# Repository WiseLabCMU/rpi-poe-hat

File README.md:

# RPi Power-over-Ethernet Hat

Give your RPi-0 ethernet and Power-ver-Ethernet (POE).  The hat uses the ENC28J60 chipset from Microchip to provide an 10Base-T 802.3af compatible interface for your RPi over SPI. The board negotiates power from your POE-enabled switch shared between 5V and 3.3V outputs at up to 9 Watts.

## Hardware Overview

### Jumpers

Placing a 0603 jumper across J1 pulls the EEPROM WP line high, preventing writes.

J2 can be used to choose a chip select on the SPI bus. By default, CS0 is connected by a trace under one of the jumpers. To change it, cut the trace with a hobby knife and place a 0603 jumper across the right-most pads in the previous picture

## Configuring your RPi

For the latest Raspbian image, go to https://www.raspberrypi.org/downloads/raspbian/. 

### Enable SPI

1. run `raspi-config` 
2. select `9 Advanced Options`
3. select `A6 SPI`
4. select `yes` to enbale SPI
5. select `yes` to automaticaly load kernel module
6. select `<Finish>`
7. select `yes` to reboot

### Enable ENC28J60 Overlay

Add the this line to the `/boot/congig.txt`:

`dtoverlay=enc28j60`

After this line is added the Raspberry Pi will automatically load the device on boot.

## Files and Directories

`hardware/RPI0E.sch` - Eagle CAD schematic for the hat.

`hardware/RPI0E.brd` - Eagle CAD board for the hat.

`hardware/bom.xlsx` - Spreadsheet with bill of materials

`hardware/datasheets/` - datasheets for the board components, as well as some part drawings.

For information on EEPROM configuration visit https://github.com/raspberrypi/hats .

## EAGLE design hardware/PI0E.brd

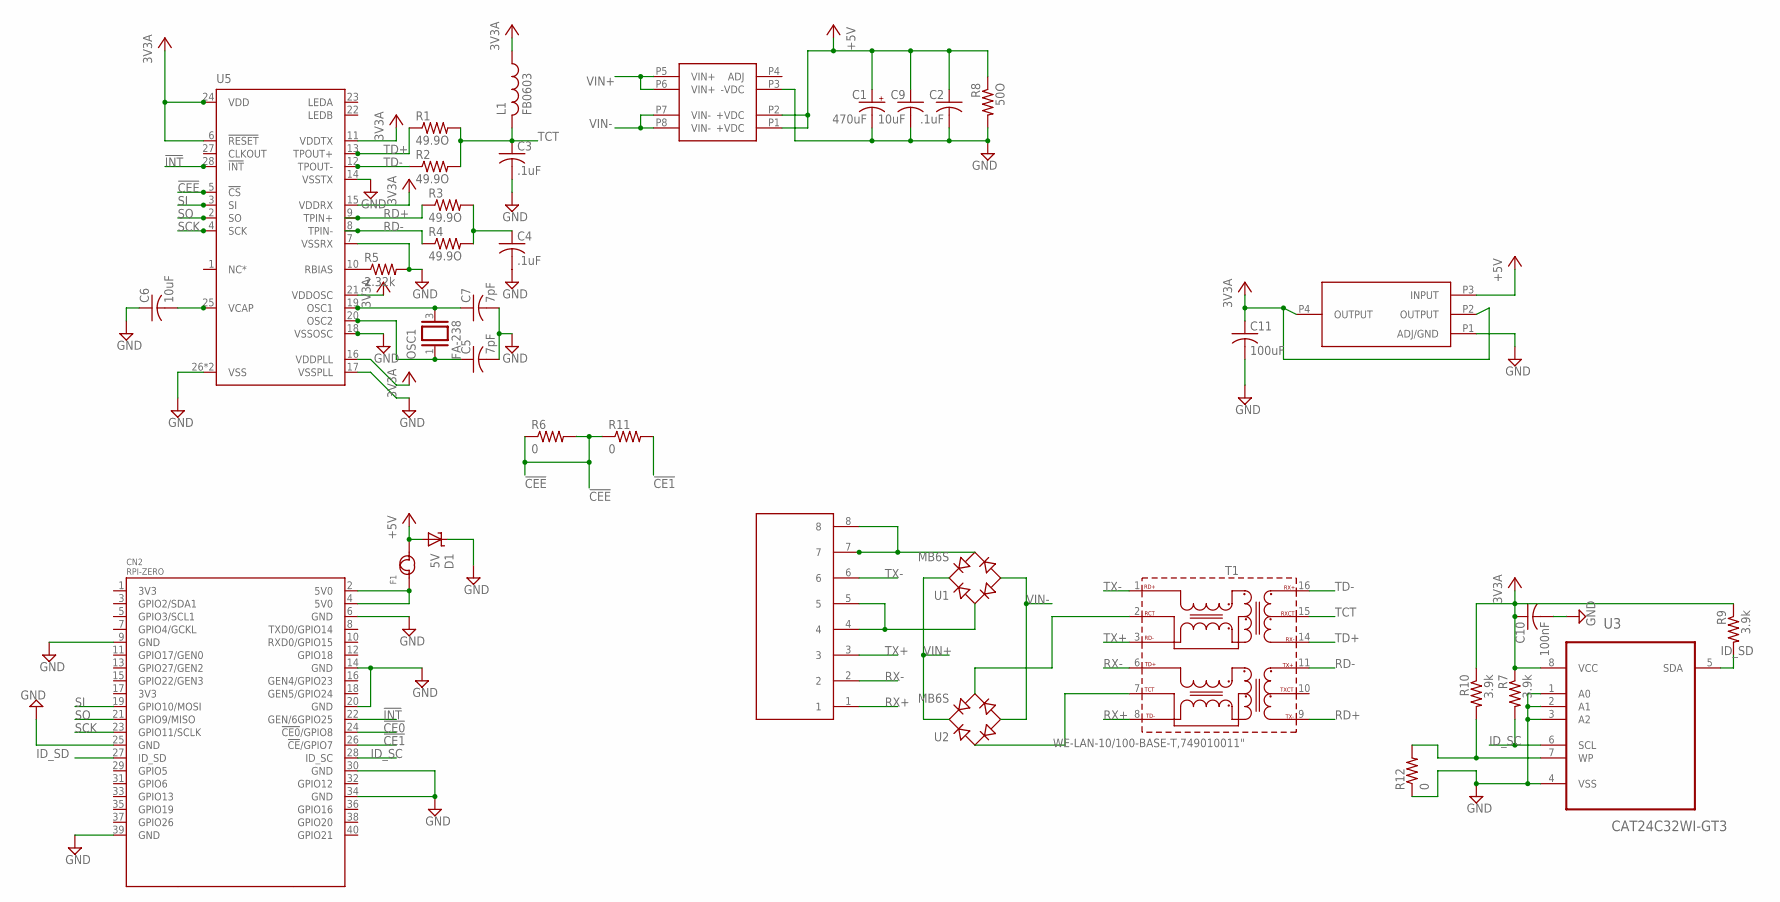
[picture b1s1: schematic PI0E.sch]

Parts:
C1: 470uF; PANASONIC_F
C2, C3, C4: .1uF; C0603
C5, C7: 7pF; C0603
C6, C9: 10uF; C0603
C10: 100nF; C0603
C11: 100uF; C0805
CN1: RJCSEX38X01XRJCSEX38X01X; RJCSEX38X01X
CN2: RPI-ZERO; RASPBERRYPI_BASTELSTUBE_V13_RASPI_BOARD_B+_FULL
D1: 5V; SMBJ
F1: FUSE'1812'; F1812
L1: FB0603; R0603
OSC1: FA-238
R1, R2, R3, R4: 49.9O; R0603
R5: 2.32k; R0603
R6, R11, R12: 0; R0603
R7, R9, R10: 3.9k; R0603
R8: 50O; R0603
T1: WE-LAN-10/100-BASE-T,749010011"; 749010011
U1, U2: MB6S; SOIC-4
U3: CAT24C32WI-GT3; SOIC127P600X175-8N
U4: TLV1117TLV1117DCY; SOT-223
U5: ENC28J60QFN28-ML_6X6MM; QFN28-ML_6X6MM
U6: AG9800AG9800M; AG9800M

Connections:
5V0@1: CN2.2 (5V0), CN2.4 (5V0), F1.1
!CE0: CN2.24 (!CE0!/GPIO8)
!CE1: CN2.26 (!CE!/GPIO7), R11.2
!CEE: R6.1, R6.2, R11.1, U5.5 (!CS)
!INT: CN2.22 (GEN/6GPIO25), U5.28 (!INT)
+3V3: C10.1, C11.1, L1.1, R7.1, R9.1, R10.1, U3.8 (VCC), U4.P2 (OUTPUT), U4.P4 (OUTPUT), U5.6 (!RESET), U5.11 (VDDTX), U5.15 (VDDRX), U5.16 (VDDPLL), U5.21 (VDDOSC), U5.24 (VDD)
+5V: C1.+, C2.1, C9.1, D1.A, F1.2, R8.1, U4.P3 (INPUT), U6.P1 (+VDC), U6.P2 (+VDC)
GND: C1.-, C2.2, C3.2, C4.2, C5.2, C6.1, C7.2, C9.2, C10.2, C11.2, CN2.6 (GND), CN2.9 (GND), CN2.14 (GND), CN2.20 (GND), CN2.25 (GND), CN2.30 (GND), CN2.34 (GND), CN2.39 (GND), D1.C, R5.2, R8.2, R12.1, U3.1 (A0), U3.2 (A1), U3.3 (A2), U3.4 (VSS), U4.P1 (ADJ/GND), U5.7 (VSSRX), U5.14 (VSSTX), U5.17 (VSSPLL), U5.18 (VSSOSC), U5.26 (VSS), U5.EXP (VSS), U6.P3 (-VDC)
ID_SC: CN2.28 (ID_SC), R7.2, U3.6 (SCL)
ID_SD: CN2.27 (ID_SD), R9.2, U3.5 (SDA)
unnamed: T1.7 (TCT), U2.~1 (AC1)
unnamed: R10.2, R12.2, U3.7 (WP)
unnamed: CN1.7, CN1.8, U1.~2 (AC2)
unnamed: CN1.4, CN1.5, U1.~1 (AC1)
unnamed: T1.2 (RCT), U2.~2 (AC2)
unnamed: C7.1, OSC1.3 (2), U5.19 (OSC1)
unnamed: C5.1, OSC1.1, U5.20 (OSC2)
unnamed: C6.2, U5.25 (VCAP)
unnamed: C4.1, R3.2, R4.2
unnamed: R5.1, U5.10 (RBIAS)
RD+: R3.1, T1.9 (TX-), U5.9 (TPIN+)
RD-: R4.1, T1.11 (TX+), U5.8 (TPIN-)
RX+: CN1.1, T1.8 (TD-)
RX-: CN1.2, T1.6 (TD+)
SCK: CN2.23 (GPIO11/SCLK), U5.4 (SCK)
SI: CN2.19 (GPIO10/MOSI), U5.3 (SI)
SO: CN2.21 (GPIO9/MISO), U5.2 (SO)
TCT: C3.1, L1.2, R1.2, R2.2, T1.15 (RXCT)
TD+: R1.1, T1.14 (RX-), U5.13 (TPOUT+)
TD-: R2.1, T1.16 (RX+), U5.12 (TPOUT-)
TX+: CN1.3, T1.3 (RD-)
TX-: CN1.6, T1.1 (RD+)
VIN+: U1.+, U2.+, U6.P5 (VIN+), U6.P6 (VIN+)
VIN-: U1.-, U2.-, U6.P7 (VIN-), U6.P8 (VIN-)

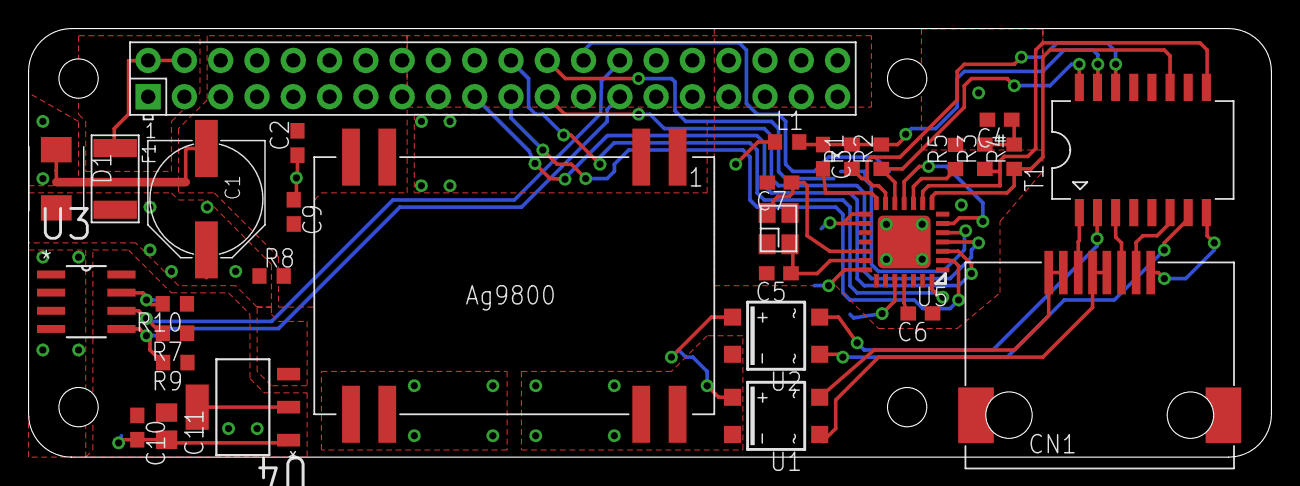
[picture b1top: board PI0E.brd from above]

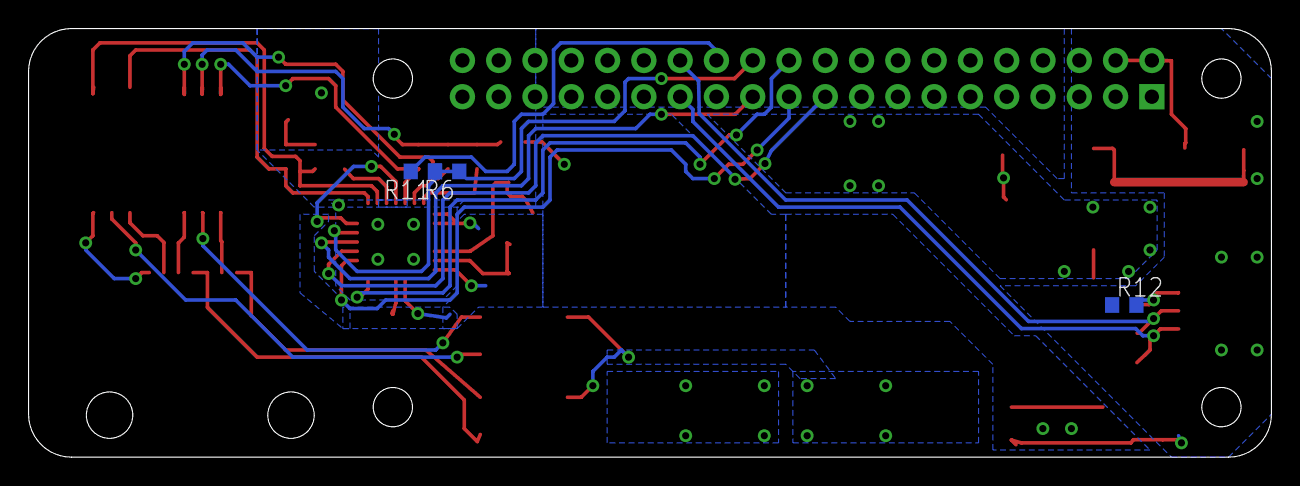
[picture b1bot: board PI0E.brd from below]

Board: 2 copper layers, 87.0 x 30.0 mm, 35 parts (3 on the bottom side), 33 nets.

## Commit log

2016-04-26 second commit
2016-04-26 Added datasheets, schematic/board, and bom.
2016-04-26 added readme.md
2016-05-08 Cleaning up routing
2016-05-09 updated drill sizes
2016-05-09 Laid ground plane
2016-05-09 No more air wires
2016-05-09 some cleaning of traces
2016-05-10 copper pour for the 3.3v regulator. A few cleaned traces.
2016-05-10 cleared drc issues, cleaned traces
2016-05-10 cleaned traces
2016-05-11 agr traces
2016-05-11 adde files
2016-05-13 fixed missing RX line
2016-05-18 fixed encj rx/tx power lines. and switch v+ v- pins into the poe module.
2016-05-18 Updated bom
2016-05-18 update to bom. last air wires taken care of on board
2016-05-18 lengthened qfn pins, fixed drc errors
2016-05-18 cleaning traces
2016-07-01 Initial ENC28J60 fixes: added missing pins and thermal vias, enlarged QFN pads and soldermask exclusions, and rerouted RESET to TP1
2016-07-05 Fixed marking size
2016-07-05 Fixed right angle at ocillator
2016-07-05 Improved wire appearence
2016-07-26 Changed layout to match RPi 0 form factor more closely
2016-07-26 Fixed silkscreen layer
2016-07-26 gerbers
2016-08-16 Changed default CE trace to CE0
2016-08-30 Changed cap from 0603 to 0805
2017-05-17 added gitignore
2017-05-17 added basic descriptions
2017-05-20 moved PCB files to the hardware foldr
2017-05-20 fixed minor readme errors
2017-05-22 Completed software config instructions
2017-05-22 Added jumper instructions

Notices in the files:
parts and their libraries:
EagleLibrary_Wuerth_Elektronik_eiSos_rev: Copyright: Würth Elektronik
